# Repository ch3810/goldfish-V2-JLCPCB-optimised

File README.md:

# Goldfish V2 - Orderable fully assembled via JLCPCB with 4L and 2L versions.

**Note: This branch contains the design for Goldfish v2. It has been modified from the original design (Credit: Lucas Jansen) to allow for compatible parts in the LCSC/JLCPCB library. 
Using the BOM, it will be possible to get a fully assembled design (outputs in cad/production). There are 2 project files which are based on specific kicad_sch and kicad_pcb files** 

**To open and work on the 2L version, open goldfish_2L.kicad_pro.**  
**To work on the 4L version, open goldfish.kicad_pro.**

**Only open the associated kicad_pcb file once the project is opened.** 

**The 4L version is highly recommended as the cost is almost the same and the signal integrity will be higher due to the full internal planes. The Goldfish v1 design files are available in the [v1 branch].**

---
Goldfish is a Pro Micro compatible microcontroller board designed for use in mechanical keyboards. It is based on the same Atmel ATMega32U4 chip and is programmable using the Arduino IDE or a keyboard specific firmware such as TMK or QMK. Of course it is perfectly usable for any other electronics projects too, not just keyboards.

![preview]

## Links

- [PCB Source Files]

- [Schematic]

- [BOM]

## Features

- Lower board profile with the mid-mounted USB-C connector
- Two internal pins make the USB data lines easily accessible
- USB-C is more durable, reversible and just plain cool
- 5 additional pins on the bottom edge of the board
- Pin-compatible with the original Pro Micro
- Sturdier through-hole USB connector
- On board ESD protection for USB lines

## Changes compared to Goldfish v1

- Addition of on board ESD protection and fuse
- All 0603 resistors and capacitors for (slightly) easier hand assembly
- Castellated edge connectors similar to the Elite-C
- Less obscure USB-C connector
  - Use of more commonly available components in 2022
  - Choice between multiple compatible connectors and suppliers
  - Uses USB 2.0-only connector for easier and cheaper assembly

![connectors]

## Disadvantages

- No onboard RX, TX LEDs
- No onboard voltage regulator (this makes no difference for keyboards; a regulator is only required when power supplies of over 5.5V are used)

## Vendors Selling Goldfish

#### Goldfish v1 rev. C

- [BeeKeeb]

#### Comet (modified design based on Goldfish v1; see related projects) 

- [Tokas' Kable Works]

**Note:** These products are sold by 3rd party vendors and are not 'officially' endorsed by me. I'm simply listing them here for convenience.

*(Also please let me know if anything is missing from this list)*

## Related Projects

#### [Alvaro] by Ariamelon

- A modified Goldfish v1 using 0603 components instead of 0402

#### [Comet] by Tokas

- A modified Goldfish v1 using a HRO TYPE-C-31-M-12 connector

#### [Whale] by Jia Geng Chang

- A modified Goldfish v1 using a Jing 918-418K2024S40000 connector

#### [Goldfish-clone-JLCPCB] by Jeremy J Starcher

- A modified Goldfish v1 designed to meet JLCPCB's assembly requirements

#### [Elite-C] from keeb.io

- An unrelated and closed source project with similar design goals

*(Please let me know if anything is missing form this list)*

## License

Released under the Creative Commons Attribution Share-Alike 4.0 License.  
https://creativecommons.org/licenses/by-sa/4.0/  

Original Arduino Mini Design by Team Arduino.  
Arduino Pro Mini Design by Spark Fun Electronics.  
Pro Micro Design by Spark Fun Electronics.  
Goldfish Design by Lucas Jansen.  

<!-- Links -->

[v1 branch]: https://github.com/staticintlucas/goldfish/tree/v1
[schematic]: docs/schematic.pdf
[BOM]: BOM.csv
[preview]: docs/preview.png
[connectors]: docs/connectors.png
[pcb source files]: cad

[beekeeb]: https://shop.beekeeb.com/product/goldfish-rev-c-open-source-pro-micro-replacement/
[tokas' kable works]: https://shop.tokas.co.uk/product/comet-usb-c-microcontroller/

[alvaro]: https://github.com/Ariamelon/Alvaro
[comet]: https://github.com/vattern/comet
[whale]: https://github.com/JiaGengChang/Whale
[elite-c]: https://keeb.io/products/elite-c-low-profile-version-usb-c-pro-micro-replacement-atmega32u4
[goldfish-clone-jlcpcb]: https://github.com/JeremyJStarcher/Goldfish-clone-JLCPCB

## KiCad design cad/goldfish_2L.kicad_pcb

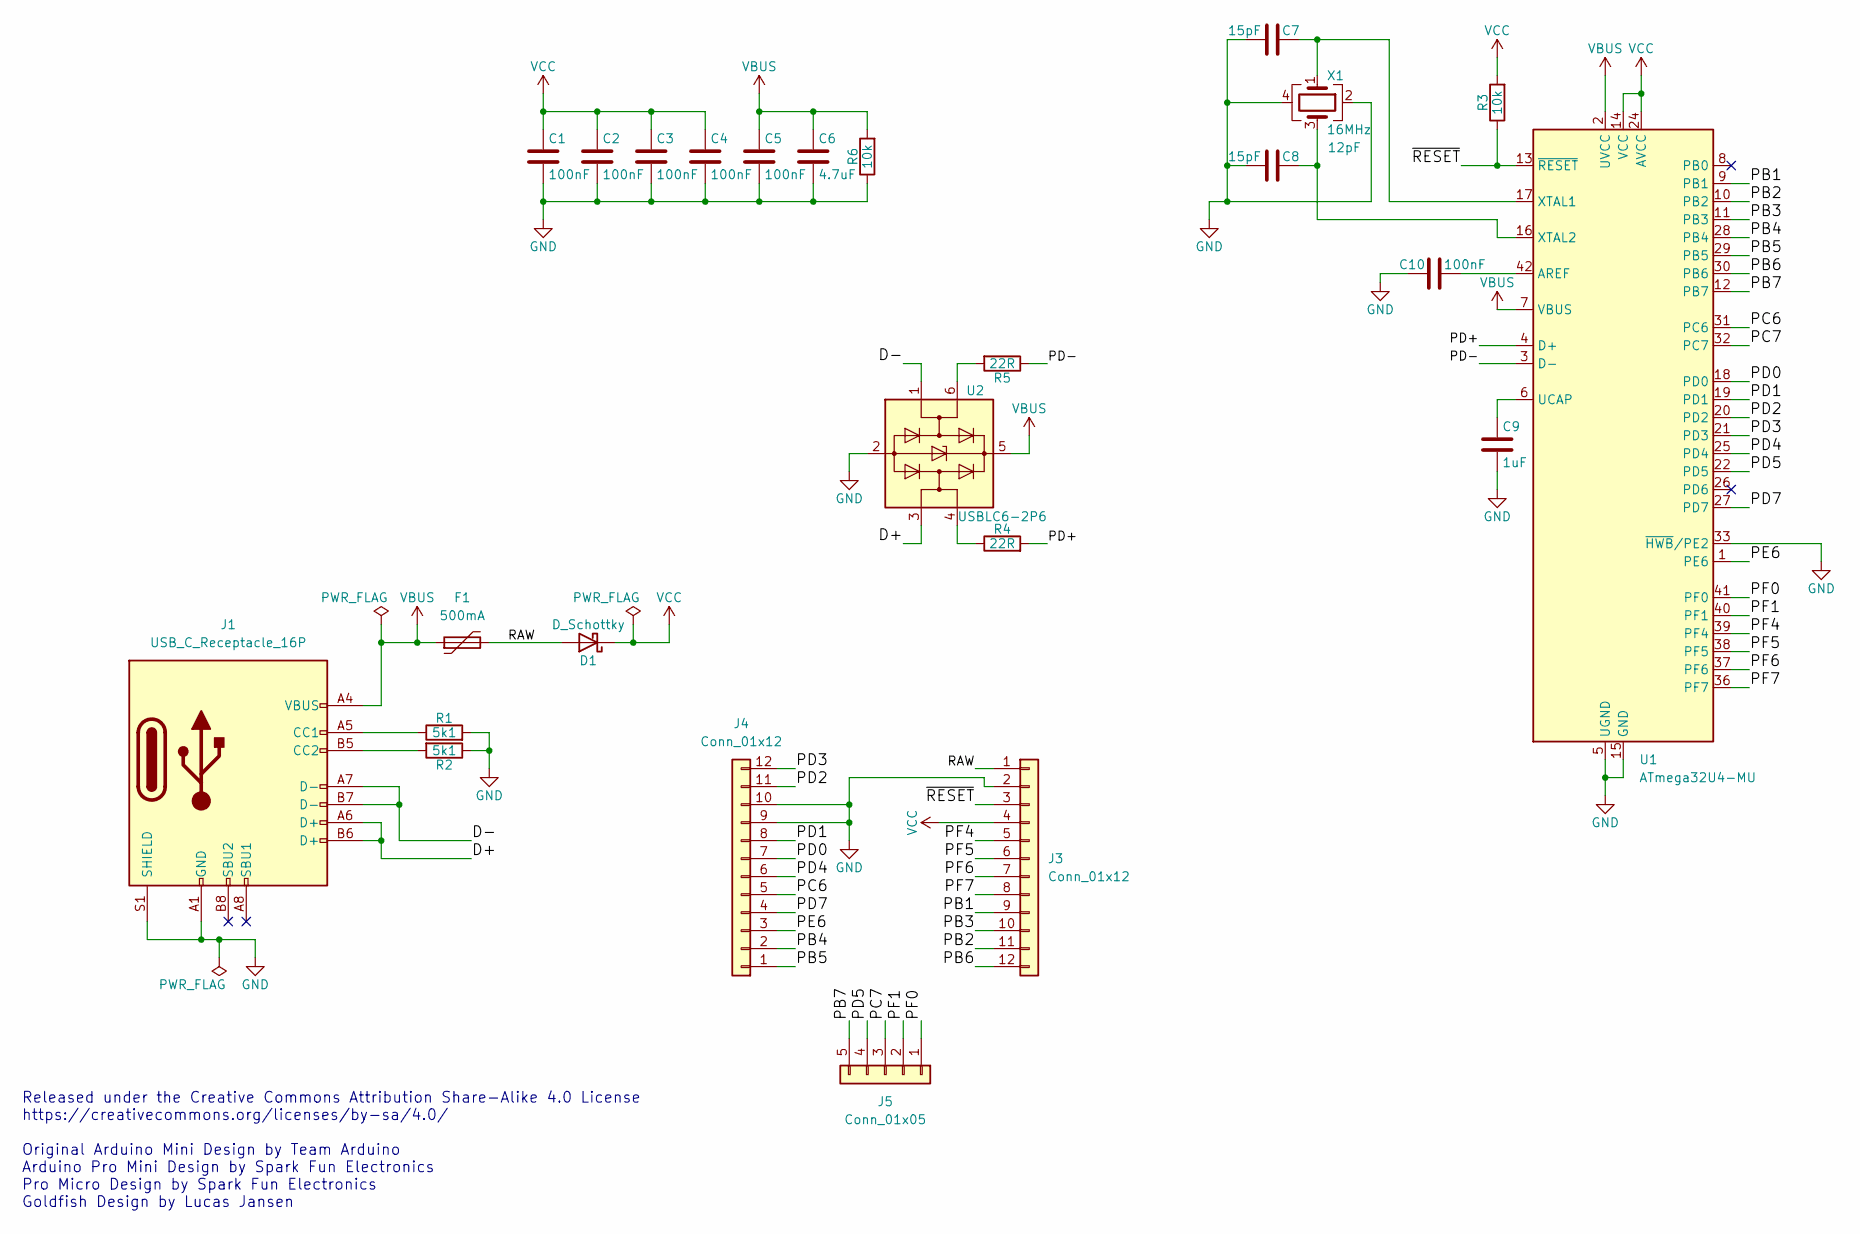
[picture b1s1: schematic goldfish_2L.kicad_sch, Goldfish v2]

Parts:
C1, C2, C3, C4, C5, C10: 100nF; C_0402_1005Metric; Tolerance 5%; MPN FN15X104J160PNG; JLCPCB C363530
C6: 4.7uF; C_0805_2012Metric; Tolerance 10%; MPN TT21X475K160CT; JLCPCB C384657
C7, C8: 15pF; C_0402_1005Metric; Tolerance 2%; MPN C0402C0G150G500NTB; JLCPCB C140684
C9: 1uF; C_0603_1608Metric; MPN CSA0603X5R105K160JT; JLCPCB C3015156
D1: D_Schottky; D_SOD-123F; MPN DSK24; JLCPCB C908229
F1: 500mA; Fuse_1206_3216Metric; MPN SMD1206P050TF/24; JLCPCB C492011
J1: USB_C_Receptacle_16P; TYPE-610-1.6-T3; MPN TYPE-610-1.6-T3; JLCPCB C2972115
J3, J4: Conn_01x12; Pins_x12
J5: Conn_01x05; Pins_x05
R1, R2: 5k1; R_0603_1608Metric; MPN RMS06JT512; JLCPCB C209245
R3, R6: 10k; R_0402_1005Metric; MPN AT0402BRD074K7L; JLCPCB C851039
R4, R5: 22R; R_0402_1005Metric; MPN ARG02FTC22R1; JLCPCB C284431
U1: ATmega32U4-MU; QFN-44-1EP_7x7mm_P0.5mm_EP5.2x5.2mm; MPN ATmega32U4-MU; JLCPCB C112161
U2: USBLC6-2P6; SOT-666; MPN USBLC6-2P6; JLCPCB C15999
X1: 16MHz; Crystal_SMD_SeikoEpson_FA238-4Pin_3.2x2.5mm; Tolerance 10ppm; MPN 7U16000E12UCG; JLCPCB C251610

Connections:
/D+: J1.A6 (D+), J1.B6 (D+), U2.3 (I/O2)
/D-: J1.A7 (D-), J1.B7 (D-), U2.1 (I/O1)
/PB1: J3.9, U1.9 (PB1)
/PB2: J3.11, U1.10 (PB2)
/PB3: J3.10, U1.11 (PB3)
/PB4: J4.2, U1.28 (PB4)
/PB5: J4.1, U1.29 (PB5)
/PB6: J3.12, U1.30 (PB6)
/PB7: J5.5, U1.12 (PB7)
/PC6: J4.5, U1.31 (PC6)
/PC7: J5.3, U1.32 (PC7)
/PD0: J4.7, U1.18 (PD0)
/PD1: J4.8, U1.19 (PD1)
/PD2: J4.11, U1.20 (PD2)
/PD3: J4.12, U1.21 (PD3)
/PD4: J4.6, U1.25 (PD4)
/PD5: J5.4, U1.22 (PD5)
/PD7: J4.4, U1.27 (PD7)
/PD+: R4.2, U1.4 (D+)
/PD-: R5.1, U1.3 (D-)
/PE6: J4.3, U1.1 (PE6)
/PF0: J5.1, U1.41 (PF0)
/PF1: J5.2, U1.40 (PF1)
/PF4: J3.5, U1.39 (PF4)
/PF5: J3.6, U1.38 (PF5)
/PF6: J3.7, U1.37 (PF6)
/PF7: J3.8, U1.36 (PF7)
/RAW: D1.2 (A), F1.2, J3.1
/~RESET: J3.3, R3.1, U1.13 (~RESET)
GND: C1.2, C2.2, C3.2, C4.2, C5.2, C6.2, C7.2, C8.2, C9.2, C10.2, J1.A1 (GND), J1.A12 (GND), J1.B1 (GND), J1.B12 (GND), J1.S1 (SHIELD), J3.2, J4.9, J4.10, R1.2, R2.1, R6.1, U1.5 (UGND), U1.15 (GND), U1.23 (GND), U1.33 (~HWB/PE2), U1.35 (GND), U1.43 (GND), U1.45 (GND), U2.2 (GND), X1.2, X1.4
unnamed: J1.A5 (CC1), R1.1
unnamed: J1.B5 (CC2), R2.2
unnamed: R4.1, U2.4 (I/O2)
unnamed: R5.2, U2.6 (I/O1)
unnamed: C10.1, U1.42 (AREF)
unnamed: C9.1, U1.6 (UCAP)
unnamed: C7.1, U1.17 (XTAL1), X1.1
unnamed: C8.1, U1.16 (XTAL2), X1.3
VBUS: C5.1, C6.1, F1.1, J1.A4 (VBUS), J1.A9 (VBUS), J1.B4 (VBUS), J1.B9 (VBUS), R6.2, U1.2 (UVCC), U1.7 (VBUS), U2.5 (VBUS)
VCC: C1.1, C2.1, C3.1, C4.1, D1.1 (K), J3.4, R3.2, U1.14 (VCC), U1.24 (AVCC), U1.34 (VCC), U1.44 (AVCC)

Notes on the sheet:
Released under the Creative Commons Attribution Share-Alike 4.0 License https://creativecommons.org/licenses/by-sa/4.0/ Original Arduino Mini Design by Team Arduino Arduino Pro Mini Design by Spark Fun Electronics Pro Micro Design by Spark Fun Electronics Goldfish Design by Lucas Jansen

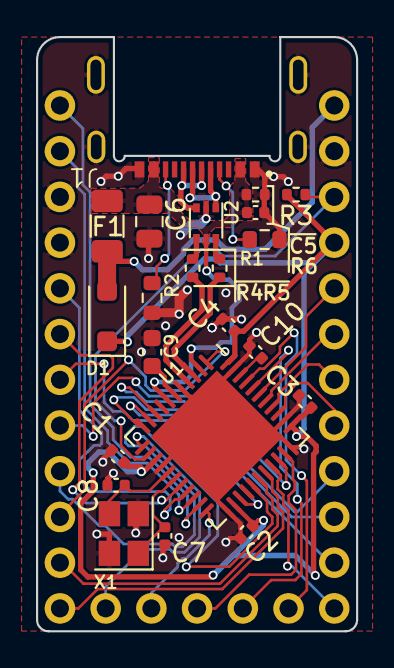
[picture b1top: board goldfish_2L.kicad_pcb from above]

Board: 2 copper layers, 17.8 x 33.0 mm, 25 parts (0 on the bottom side), 40 nets.

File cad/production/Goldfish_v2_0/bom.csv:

Designator,Footprint,Quantity,Value,LCSC Part #
"C1, C10, C2, C3, C4, C5",0402,6,100nF,C363530
C6,0805,1,4.7uF,C384657
"C7, C8",0402,2,15pF,C140684
C9,0603,1,1uF,C3015156
D1,D_SOD-123F,1,D_Schottky,C908229
F1,1206,1,500mA,C492011
J1,TYPE-610-1.6-T3,1,USB_C_Receptacle_16P,C2972115
"J3, J4",Pins_x12,2,Conn_01x12,
J5,Pins_x05,1,Conn_01x05,
"R1, R2",0603,2,5k1,C209245 
"R3, R6",0402,2,10k,C851039
"R4, R5",0402,2,22R,C284431
U1,QFN-44-1EP_7x7mm_P0.5mm_EP5.2x5.2mm,1,ATmega32U4-MU,C112161
U2,SOT-666,1,USBLC6-2P6,C15999
X1,Crystal_SMD_SeikoEpson_FA238-4Pin_3.2x2.5mm,1,16MHz,C251610

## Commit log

2023-09-23 Initial release - contains a 4L version and a 2L version project based on the same schematic, all libraries combined into one
2023-09-23 corrected front silkscreens and added schematic PDF files
2023-09-23 made a second kicad_sch file to simplify netlist process as it can be harder to manage otherwise. Also added production files for JLCPCB and gerbers inside cad/production folder
